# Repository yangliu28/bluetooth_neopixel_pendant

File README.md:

# bluetooth_neopixel_pendant

The circuit is designed on top of Arduino Micro, but changing the I/O level and clock to 3.3v and 8MHz respectively. The MCU has been loaded the same bootloader and fuses with [Sparkfun Pro Micro](https://www.sparkfun.com/products/12587). To upload program, [install Sparkfun Arduino Boards](https://github.com/sparkfun/Arduino_Boards#installation-instructions) to your Arduino IDE, and choose "Sparkfun Pro Micro" as board, and "Atmega32U4 (3.3v, 8 MHz)" as processor. The onboard bluetooth module HC-06 works only with Android and Windows, not iOS.

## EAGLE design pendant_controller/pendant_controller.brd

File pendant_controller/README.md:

## Hardware design

ATMEGA32U4 has built-in USB interface, for easily reprogramming the device without a USB to serial converter. The system is powered at 3.3v and clocked at 8MHz. Bluetooth module is HC-06 configured in slave mode. RGB LEDs are Neopixel Nano, with a small footprint of 2.4x2.7mm.

Diameter of the circular PCB is 1.7in, radius of 850 mil.

Matlab script to generate pos and orientation of neopixels:
```
d=735;
pos=zeros(10:3);
pos(1:5,1) = 850+d*cos((90+22+34*n)*pi/180);
pos(6:10,1) = 850+d*cos((-90+22+34*n)*pi/180);
pos(1:5,2) = 850+d*sin((90+22+34*n)*pi/180);
pos(6:10,2) = 850+d*sin((-90+22+34*n)*pi/180);
pos(1:5,3) = -180+22+34*n;
pos(6:10,3) = 22+34*n;
```

### Board fix

**Reset pin of ATMEGA32U4 was be pulled up to 3V3 with a 10K resistor**

**Enable pins of two regulators for bluetooth and IMU were not working, because the voltage level of enable pin does not match output. Jumpers were used to keep regulators enabled always.**

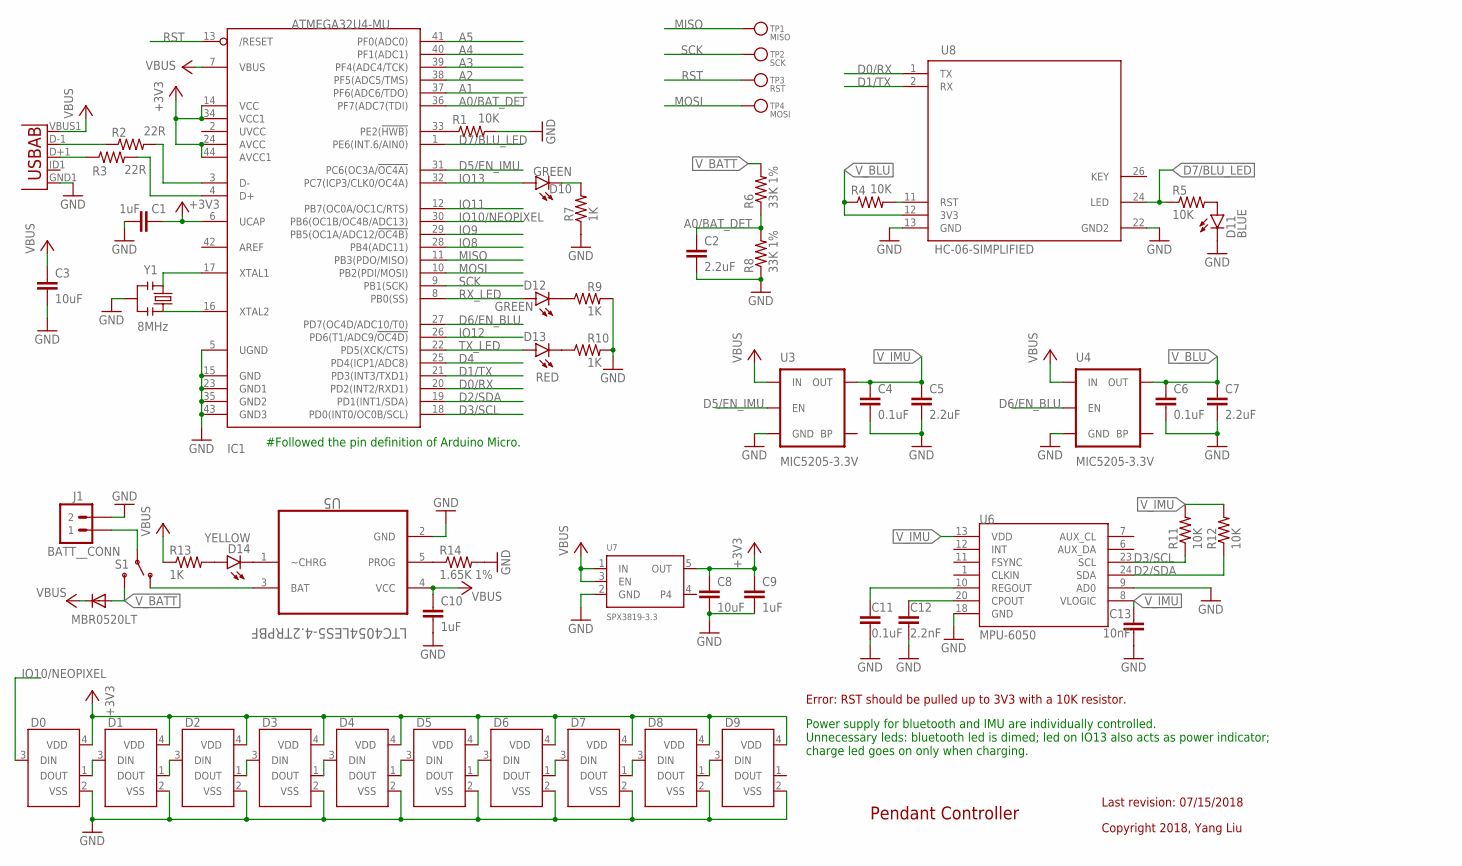
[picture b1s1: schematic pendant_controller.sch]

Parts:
C1, C9, C10: 1uF; 0603-CAP
C2, C5, C7: 2.2uF; 0402-CAP
C3, C8: 10uF; 1206
C4, C6, C11: 0.1uF; 0402-CAP
C12: 2.2nF; 0402-CAP
C13: 10nF; 0402-CAP
D0, D1, D2, D3, D4, D5, D6, D7, D8, D9: NEOPIXEL-2427; LED2427
D10, D12: GREEN; LED-0603
D11: BLUE; LED-0603
D13: RED; LED-0603
D14: YELLOW; LED-0603
D15: MBR0520LT; SOD123
IC1: ATMEGA32U4-MU; TQFN44_7MM
J1: BATT__CONN; 1X02-SMALL
R1, R4, R5, R11, R12: 10K; 0402-RES
R2, R3: 22R; 0603-RES
R6, R8: 33K 1%; 0402-RES
R7, R9, R10, R13: 1K; 0402-RES
R14: 1.65K 1%; 0402-RES
S1: SWITCH-SPDTPTH; SWITCH-SPDT
TP1: MISO; TESTPOINT_ROUND_1.5MM
TP2: SCK; TESTPOINT_ROUND_1.5MM
TP3: RST; TESTPOINT_ROUND_1.5MM
TP4: MOSI; TESTPOINT_ROUND_1.5MM
U2: USB""; USB-MICRO-SMD
U3, U4: MIC5205-3.3V; SOT23-5
U5: LTC4054LES5-4.2TRPBF; SOT95P280X100-5N
U6: MPU-6050; QFN-24
U7: SPX3819-3.3; SOT23-5
U8: HC-06-SIMPLIFIED; HC-06_SMD
Y1: 8MHz; RESONATOR-SMD

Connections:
+3V3: C1.1, C8.1, C9.1, D0.4 (VDD), D1.4 (VDD), D2.4 (VDD), D3.4 (VDD), D4.4 (VDD), D5.4 (VDD), D6.4 (VDD), D7.4 (VDD), D8.4 (VDD), D9.4 (VDD), IC1.6 (UCAP), IC1.14 (VCC), IC1.24 (AVCC), IC1.34 (VCC1), IC1.44 (AVCC1), U7.5 (OUT)
A0/BAT_DET: C2.1, IC1.36 (PF7(ADC7(TDI)), R6.1, R8.2
A1: IC1.37 (PF6(ADC6/TDO))
A2: IC1.38 (PF5(ADC5/TMS))
A3: IC1.39 (PF4(ADC4/TCK))
A4: IC1.40 (PF1(ADC1))
A5: IC1.41 (PF0(ADC0))
D0/RX: IC1.20 (PD2(INT2/RXD1)), U8.1 (TX)
D1/TX: IC1.21 (PD3(INT3/TXD1)), U8.2 (RX)
D2/SDA: IC1.19 (PD1(INT1/SDA)), R12.1, U6.24 (SDA)
D3/SCL: IC1.18 (PD0(INT0/OC0B/SCL)), R11.1, U6.23 (SCL)
D4: IC1.25 (PD4(ICP1/ADC8))
D5/EN_IMU: IC1.31 (PC6(OC3A/!OC4A)), U3.3 (EN)
D6/EN_BLU: IC1.27 (PD7(OC4D/ADC10/T0)), U4.3 (EN)
D7/BLU_LED: IC1.1 (PE6(INT.6/AIN0)), R5.1, U8.24 (LED)
GND: C1.2, C2.2, C3.2, C4.2, C5.2, C6.2, C7.2, C8.2, C9.2, C10.2, C11.2, C12.2, C13.2, D0.2 (VSS), D1.2 (VSS), D2.2 (VSS), D3.2 (VSS), D4.2 (VSS), D5.2 (VSS), D6.2 (VSS), D7.2 (VSS), D8.2 (VSS), D9.2 (VSS), D11.C, IC1.5 (UGND), IC1.15 (GND), IC1.23 (GND1), IC1.35 (GND2), IC1.43 (GND3), J1.2, R1.2, R7.1, R8.1, R9.2, R10.2, R14.2, U2.GND1 (GND), U3.2 (GND), U4.2 (GND), U5.2 (GND), U6.9 (AD0), U6.18 (GND), U7.2 (GND), U8.13 (GND), U8.22 (GND2), Y1.2
IO8: IC1.28 (PB4(ADC11))
IO9: IC1.29 (PB5(OC1A/ADC12/!OC4B))
IO10/NEOPIXEL: D0.3 (DIN), IC1.30 (PB6(OC1B/OC4B/ADC13))
IO11: IC1.12 (PB7(OC0A/OC1C/RTS))
IO12: IC1.26 (PD6(T1/ADC9/!OC4D))
IO13: D10.A, IC1.32 (PC7(ICP3/CLK0/OC4A))
MISO: IC1.11 (PB3(PDO/MISO)), TP1.P$1
MOSI: IC1.10 (PB2(PDI/MOSI)), TP4.P$1
unnamed: S1.1 (O), U5.3 (BAT)
unnamed: J1.1, S1.2
unnamed: R2.1, U2.D-1 (D-)
unnamed: D14.A, R13.2
unnamed: R3.1, U2.D+1 (D+)
unnamed: IC1.33 (PE2(!HWB)), R1.1
unnamed: IC1.4 (D+), R3.2
unnamed: R14.1, U5.5 (PROG)
unnamed: D14.C, U5.1 (~CHRG)
unnamed: D0.1 (DOUT), D1.3 (DIN)
unnamed: IC1.16 (XTAL2), Y1.3
unnamed: IC1.17 (XTAL1), Y1.1
unnamed: IC1.3 (D-), R2.2
unnamed: D12.C, R9.1
unnamed: D13.C, R10.1
unnamed: C12.1, U6.20 (CPOUT)
unnamed: C11.1, U6.10 (REGOUT)
unnamed: R4.2, U8.11 (RST)
unnamed: D10.C, R7.2
unnamed: D11.A, R5.2
unnamed: D1.1 (DOUT), D2.3 (DIN)
unnamed: D2.1 (DOUT), D3.3 (DIN)
unnamed: D3.1 (DOUT), D4.3 (DIN)
unnamed: D4.1 (DOUT), D5.3 (DIN)
unnamed: D5.1 (DOUT), D6.3 (DIN)
unnamed: D6.1 (DOUT), D7.3 (DIN)
unnamed: D7.1 (DOUT), D8.3 (DIN)
unnamed: D8.1 (DOUT), D9.3 (DIN)
RST: IC1.13 (/RESET), TP3.P$1
RX_LED: D12.A, IC1.8 (PB0(SS))
SCK: IC1.9 (PB1(SCK)), TP2.P$1
TX_LED: D13.A, IC1.22 (PD5(XCK/CTS))
VBUS: C3.1, C10.1, D15.C, IC1.7 (VBUS), R13.1, U2.VBUS1 (VBUS), U3.1 (IN), U4.1 (IN), U5.4 (VCC), U7.1 (IN), U7.3 (EN)
V_BATT: D15.A, R6.2, S1.3 (S)
V_BLU: C6.1, C7.1, R4.1, U4.5 (OUT), U8.12 (3V3)
V_IMU: C4.1, C5.1, C13.1, R11.2, R12.2, U3.5 (OUT), U6.8 (VLOGIC), U6.13 (VDD)

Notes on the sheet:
Last revision: 07/15/2018
Copyright 2018, Yang Liu
Pendant Controller
#Followed the pin definition of Arduino Micro.
Power supply for bluetooth and IMU are individually controlled. Unnecessary leds: bluetooth led is dimed; led on IO13 also acts as power indicator; charge led goes on only when charging.
Error: RST should be pulled up to 3V3 with a 10K resistor.

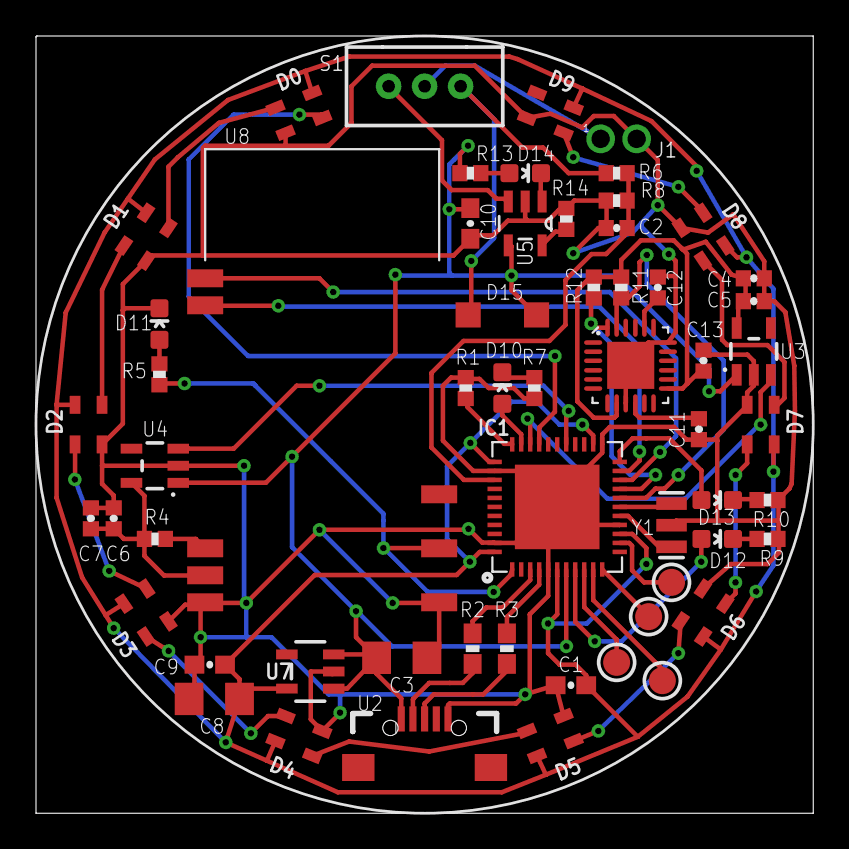
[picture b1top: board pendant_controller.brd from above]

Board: 2 copper layers, 43.2 x 43.2 mm, 58 parts (0 on the bottom side), 50 nets.

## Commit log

2018-12-02 initial commit
    board design and case CAD
2018-12-03 demo program
2018-12-03 fix regulator not enabled problem
2018-12-03 update bt not working on ios
2018-12-03 pass bluetooth test
2018-12-03 update board fix image
2018-12-04 debug print
2018-12-05 add distinct colors
2018-12-05 bluetooth command format
2018-12-06 control mode
2018-12-09 update color settings
2018-12-09 add color mapping
2018-12-09 update gravity mode
2018-12-31 battery voltage measurement
2019-01-22 update final picture

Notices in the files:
parts and their libraries:
SparkFun-Capacitors: Licensing: Creative Commons ShareAlike 4.0 International - https://creativecommons.org/licenses/by-sa/4.0
microbuilder: This work is placed in the public domain, and may be freely used for commercial and non-commercial work with the following conditions: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
